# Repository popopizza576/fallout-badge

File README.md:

ts my fallout badge, we make a badge for our hackclub trip to Shenzhen

it has a usb edge connector with LEDs
you need to use 18 0805 220 ohm resistors and 18 0805 smd LEDs

popo on slack

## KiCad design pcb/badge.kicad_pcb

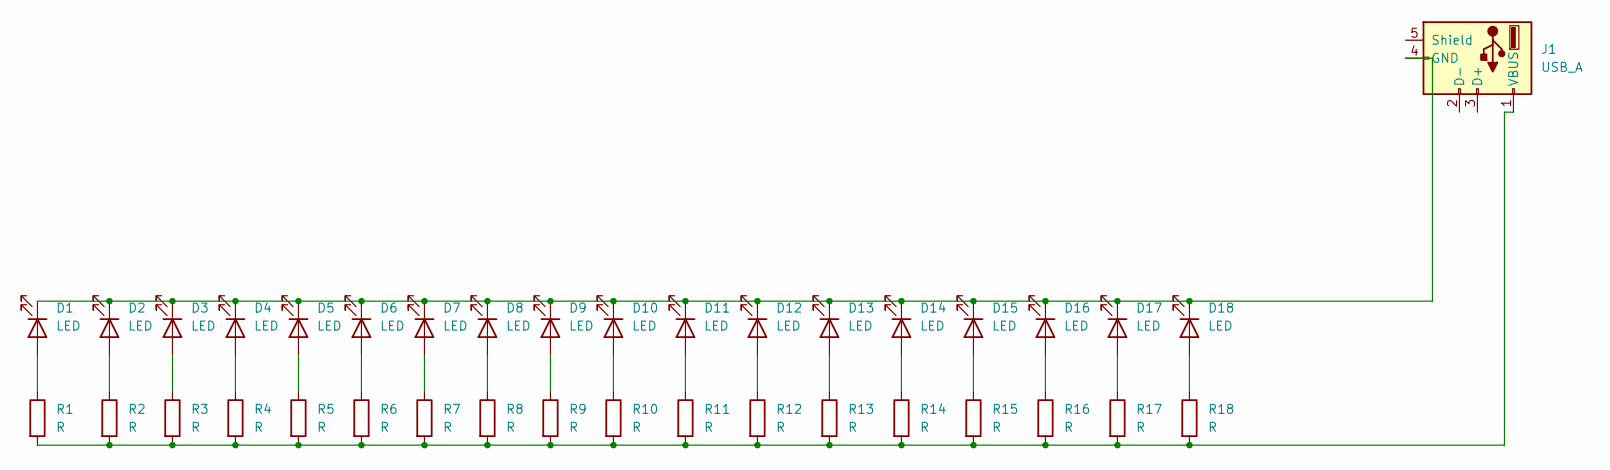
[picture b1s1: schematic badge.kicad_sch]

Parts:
D1, D2, D3, D4, D5, D6, D7, D8, D9, D10, D11, D12, D13, D14, D15, D16, D17, D18: LED; LED_0805_2012Metric_Pad1.15x1.40mm_HandSolder
J1: USB_A; edge_connector
R1, R2, R3, R4, R5, R6, R7, R8, R9, R10, R11, R12, R13, R14, R15, R16, R17, R18: R; R_0805_2012Metric_Pad1.20x1.40mm_HandSolder

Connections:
unnamed: D1.2 (A), R1.1
unnamed: D1.1 (K), D2.1 (K), D3.1 (K), D4.1 (K), D5.1 (K), D6.1 (K), D7.1 (K), D8.1 (K), D9.1 (K), D10.1 (K), D11.1 (K), D12.1 (K), D13.1 (K), D14.1 (K), D15.1 (K), D16.1 (K), D17.1 (K), D18.1 (K), J1.4 (GND)
unnamed: D2.2 (A), R2.1
unnamed: D3.2 (A), R3.1
unnamed: D4.2 (A), R4.1
unnamed: D5.2 (A), R5.1
unnamed: D6.2 (A), R6.1
unnamed: D7.2 (A), R7.1
unnamed: D8.2 (A), R8.1
unnamed: D9.2 (A), R9.1
unnamed: D10.2 (A), R10.1
unnamed: D11.2 (A), R11.1
unnamed: D12.2 (A), R12.1
unnamed: D13.2 (A), R13.1
unnamed: D14.2 (A), R14.1
unnamed: D15.2 (A), R15.1
unnamed: D16.2 (A), R16.1
unnamed: D17.2 (A), R17.1
unnamed: D18.2 (A), R18.1
unnamed: J1.1 (VBUS), R1.2, R2.2, R3.2, R4.2, R5.2, R6.2, R7.2, R8.2, R9.2, R10.2, R11.2, R12.2, R13.2, R14.2, R15.2, R16.2, R17.2, R18.2

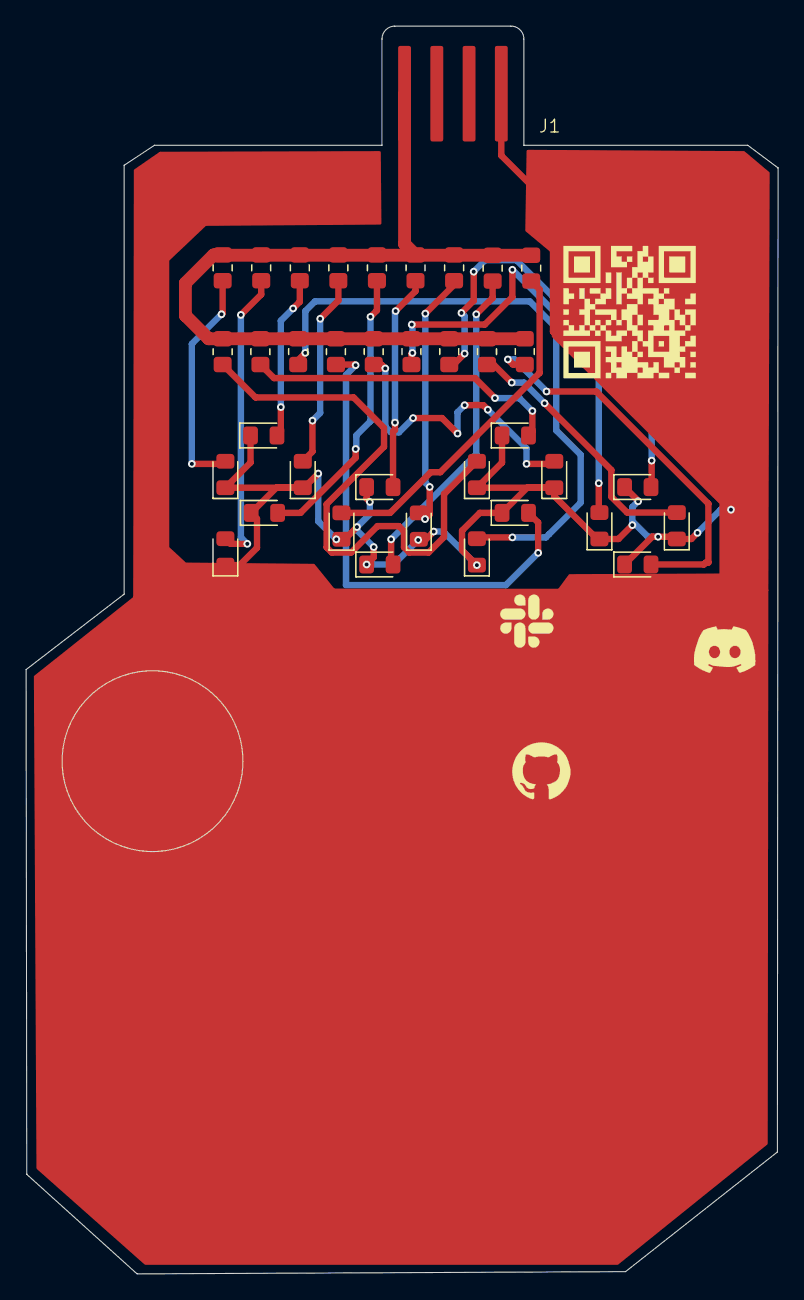
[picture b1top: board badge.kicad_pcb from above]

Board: 2 copper layers, 58.3 x 96.7 mm, 37 parts (0 on the bottom side), 20 nets.
